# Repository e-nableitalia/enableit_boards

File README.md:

# enable-it
e-Nable Italia Bionic Platform

This project aims to create a general purpose hardware platform that can be used to develop bionic/electronics controlled devices

## Boards
### Controllers - controller boards with a general purpose CPU, exposing a standard bus interface (see B2BCB specifications)
* ESP32 Wroom board Rev. B - ESP32 S3 based 

### Debug - debug, testing boards
* Debug Board Rev. A, mating board useful for debug and testing purposes

## Project directory layout
- docs, contains general documents
- schematics,  contains schematics in PDF format
- build, contains CAM Output files for board production
- EAGLE, contains project EAGLE files

## Project updates
220913 - repo init, added project doc & rev. 0.9 of ESP32 controller board

220922 - added debug board, added Rev. B of control board

220927 - updated debug board to Rev. A (added bottom connectors to allow tests of stacked boards)

230305 - added EMG Module - Rev B, changed name to enable-it

## KNOWN ISSUES

- ESP32 Controller board flash programming problem, rework required to fix this issue 
- Power connectors are not correctly aligned in all the boards, rework required to fix this issue
- Wrong height of 40pin connectors (4mm instead of 3mm)
- EMG Module power issue: short circuitt between AVDD & AVSS (PS$32 AVSS connected to V+ instead of V-)

## LIMITATION OF LIABILITY.
UNDER NO CIRCUMSTANCES AND UNDER NO LEGAL THEORY, WHETHER TORT (INCLUDING NEGLIGENCE), CONTRACT, OR OTHERWISE, SHALL YOU, THE INITIAL DEVELOPER, ANY OTHER CONTRIBUTOR, OR ANY DISTRIBUTOR OF COVERED CODE, OR ANY SUPPLIER OF ANY OF SUCH PARTIES, BE LIABLE TO ANY PERSON FOR ANY INDIRECT, SPECIAL, INCIDENTAL, OR CONSEQUENTIAL DAMAGES OF ANY CHARACTER INCLUDING, WITHOUT LIMITATION, DAMAGES FOR LOSS OF GOODWILL, WORK STOPPAGE, COMPUTER FAILURE OR MALFUNCTION, OR ANY AND ALL OTHER COMMERCIAL DAMAGES OR LOSSES, EVEN IF SUCH PARTY SHALL HAVE BEEN INFORMED OF THE POSSIBILITY OF SUCH DAMAGES. THIS LIMITATION OF LIABILITY SHALL NOT APPLY TO LIABILITY FOR DEATH OR PERSONAL INJURY RESULTING FROM SUCH PARTY'S NEGLIGENCE TO THE EXTENT APPLICABLE LAW PROHIBITS SUCH LIMITATION. SOME JURISDICTIONS DO NOT ALLOW THE EXCLUSION OR LIMITATION OF INCIDENTAL OR CONSEQUENTIAL DAMAGES, SO THIS EXCLUSION AND LIMITATION MAY NOT APPLY TO YOU.

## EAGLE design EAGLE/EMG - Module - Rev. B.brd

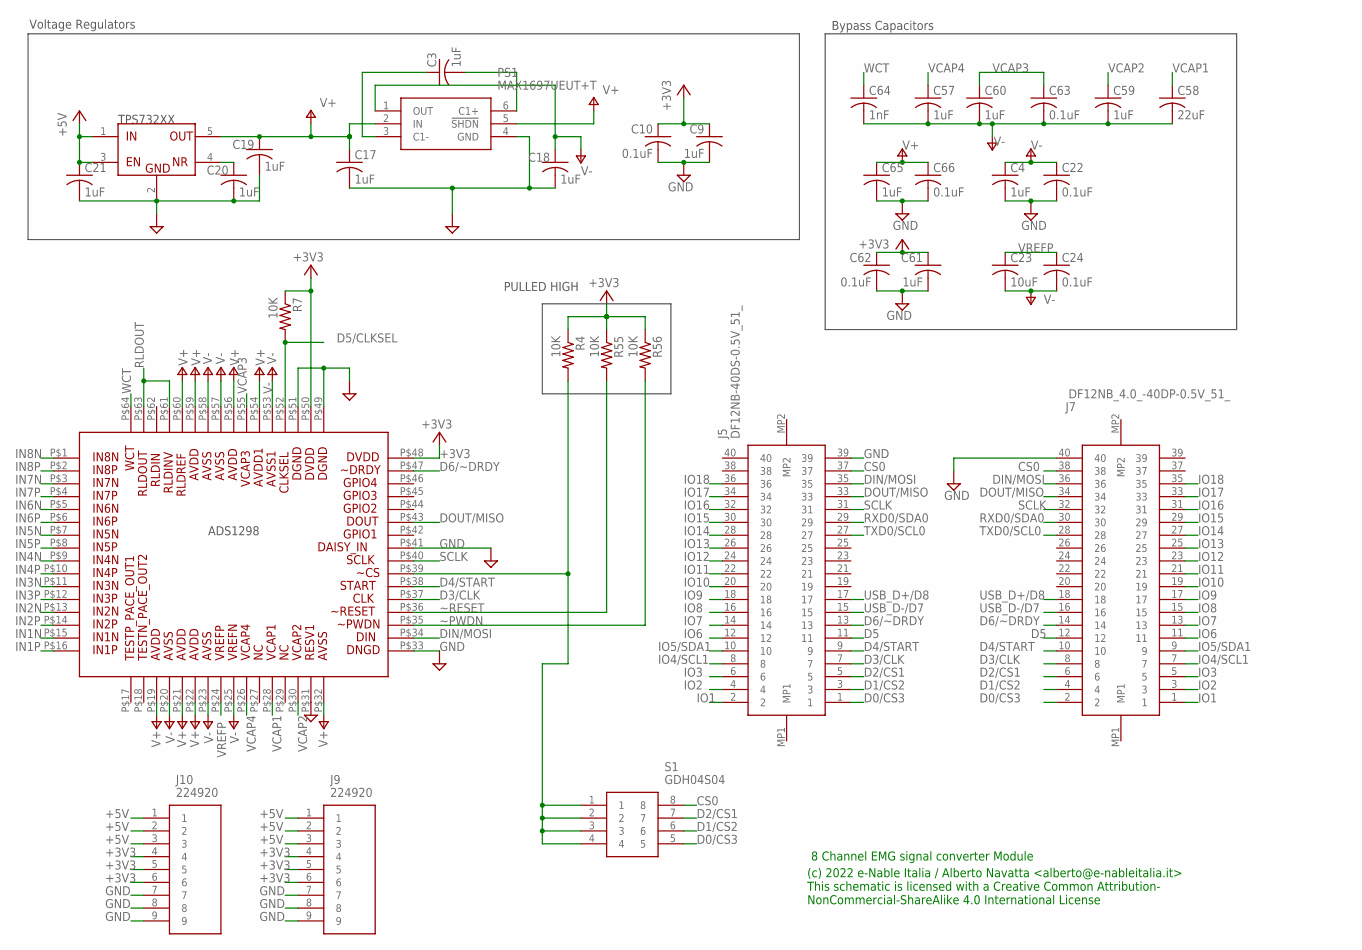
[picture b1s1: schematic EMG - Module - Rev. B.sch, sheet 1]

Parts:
C3, C4, C9, C17, C18, C19, C20, C21, C57, C59, C60, C61, C65: 1uF; C0402
C10, C22, C24, C62, C63, C66: 0.1uF; C0402
C23: 10uF; C0402
C58: 22uF; C0402
C64: 1nF; C0402
J5: DF12NB-40DS-0.5V_51_; DF12NB40DS05V51
J7: DF12NB_4.0_-40DP-0.5V_51_; DF12NB4040DP05V51
J9, J10: 224920
PS1: MAX1697UEUT+T; SOT95P280X145-6N
R4, R7, R55, R56: 10K; R0402
S1: GDH04S04; SOIC127P813X256-8N
U1: U1; TQFP-64
U21: TPS732XX; SOT23-5

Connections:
+3V3: C9.1, C10.1, C61.1, C62.1, J9.4, J9.5, J9.6, J10.4, J10.5, J10.6, R4.1, R7.1, R55.1, R56.1, U1.P$48, U1.P$50
+5V: C21.1, J9.1, J9.2, J9.3, J10.1, J10.2, J10.3, U21.1 (IN), U21.3 (EN)
CS0: J5.37, J7.38, S1.8
D0/CS3: J5.1, J7.2, S1.5
D1/CS2: J5.3, J7.4, S1.6
D2/CS1: J5.5, J7.6, S1.7
D3/CLK: J5.7, J7.8, U1.P$37
D4/START: J5.9, J7.10, U1.P$38
D5: J5.11, J7.12
D5/CLKSEL: R7.2, U1.P$52
D6/~DRDY: J5.13, J7.14, U1.P$47
DIN/MOSI: J5.35, J7.36, U1.P$34
DOUT/MISO: J5.33, J7.34, U1.P$43
GND: C4.2, C9.2, C10.2, C17.2, C18.2, C19.2, C20.2, C21.2, C22.2, C61.2, C62.2, C65.2, C66.2, J5.39, J7.40, J9.7, J9.8, J9.9, J10.7, J10.8, J10.9, PS1.4 (GND), U1.P$31, U1.P$33, U1.P$41, U1.P$49, U1.P$51, U21.2 (GND); also elsewhere on the board
IN1N: U1.P$15; also elsewhere on the board
IN1P: U1.P$16; also elsewhere on the board
IN2N: U1.P$13; also elsewhere on the board
IN2P: U1.P$14; also elsewhere on the board
IN3N: U1.P$11; also elsewhere on the board
IN3P: U1.P$12; also elsewhere on the board
IN4N: U1.P$9; also elsewhere on the board
IN4P: U1.P$10; also elsewhere on the board
IN5N: U1.P$7; also elsewhere on the board
IN5P: U1.P$8; also elsewhere on the board
IN6N: U1.P$5; also elsewhere on the board
IN6P: U1.P$6; also elsewhere on the board
IN7N: U1.P$3; also elsewhere on the board
IN7P: U1.P$4; also elsewhere on the board
IN8N: U1.P$1; also elsewhere on the board
IN8P: U1.P$2; also elsewhere on the board
IO1: J5.2, J7.1
IO2: J5.4, J7.3
IO3: J5.6, J7.5
IO4/SCL1: J5.8, J7.7
IO5/SDA1: J5.10, J7.9
IO6: J5.12, J7.11
IO7: J5.14, J7.13
IO8: J5.16, J7.15
IO9: J5.18, J7.17
IO10: J5.20, J7.19
IO11: J5.22, J7.21
IO12: J5.24, J7.23
IO13: J5.26, J7.25
IO14: J5.28, J7.27
IO15: J5.30, J7.29
IO16: J5.32, J7.31
IO17: J5.34, J7.33
IO18: J5.36, J7.35
unnamed: C3.1, PS1.3 (C1-)
unnamed: C3.2, PS1.6 (C1+)
unnamed: C20.1, U21.4 (NR)
RLDOUT: U1.P$61, U1.P$63; also elsewhere on the board
RXD0/SDA0: J5.29, J7.30
SCLK: J5.31, J7.32, U1.P$40
TXD0/SCL0: J5.27, J7.28
USB_D+/D8: J5.17, J7.18
USB_D-/D7: J5.15, J7.16
V+: C17.1, C19.1, C65.1, C66.1, PS1.2 (IN), PS1.5 (!SHDN), U1.P$19, U1.P$21, U1.P$22, U1.P$32, U1.P$54, U1.P$56, U1.P$59, U1.P$60, U21.5 (OUT)
V-: C4.1, C18.1, C22.1, C23.2, C24.2, C57.2, C58.2, C59.2, C60.2, C63.2, C64.2, PS1.1 (OUT), U1.P$20, U1.P$23, U1.P$25, U1.P$53, U1.P$57, U1.P$58
VCAP1: C58.1, U1.P$28
VCAP2: C59.1, U1.P$30
VCAP3: C60.1, C63.1, U1.P$55
VCAP4: C57.1, U1.P$26
VREFP: C23.1, C24.1, U1.P$24
WCT: C64.1, U1.P$64
~CS: R4.2, S1.1, S1.2, S1.3, S1.4, U1.P$39
~PWDN: R56.2, U1.P$35
~RESET: R55.2, U1.P$36

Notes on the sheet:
PULLED HIGH
Voltage Regulators
Bypass Capacitors
(c) 2022 e-Nable Italia / Alberto Navatta <alberto@e-nableitalia.it> This schematic is licensed with a Creative Common Attribution- NonCommercial-ShareAlike 4.0 International License
8 Channel EMG signal converter Module

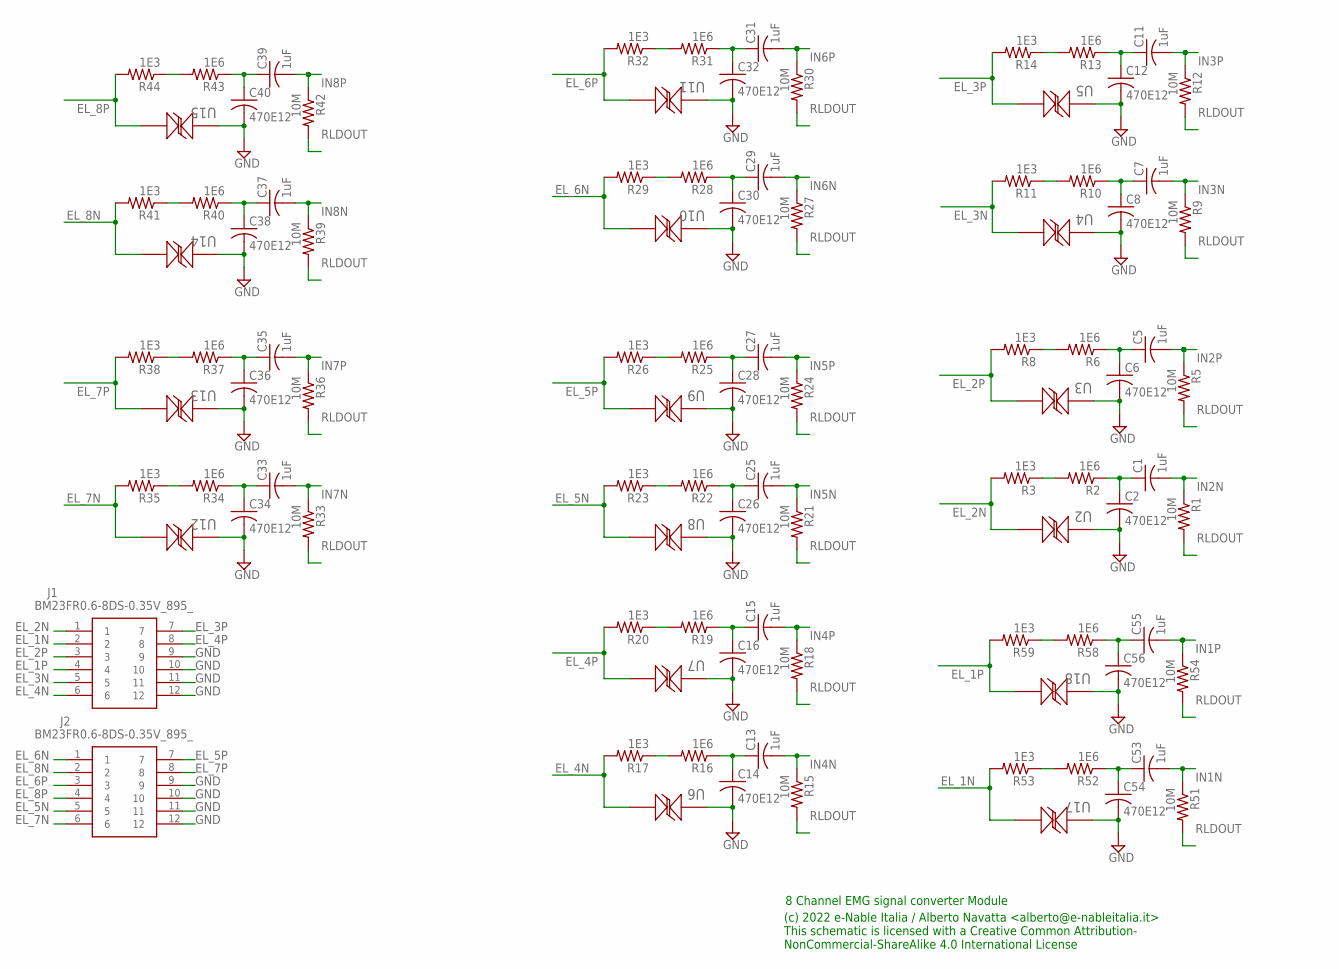
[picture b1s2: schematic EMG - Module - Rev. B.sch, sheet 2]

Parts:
C1, C5, C7, C11, C13, C15, C25, C27, C29, C31, C33, C35, C37, C39, C53, C55: 1uF; C0402
C2, C6, C8, C12, C14, C16, C26, C28, C30, C32, C34, C36, C38, C40, C54, C56: 470E12; C0402
J1, J2: BM23FR0.6-8DS-0.35V_895_; BM23FR068DS035V895
R1, R5, R9, R12, R15, R18, R21, R24, R27, R30, R33, R36, R39, R42, R51, R54: 10M; R0402
R2, R6, R10, R13, R16, R19, R22, R25, R28, R31, R34, R37, R40, R43, R52, R58: 1E6; R0402
R3, R8, R11, R14, R17, R20, R23, R26, R29, R32, R35, R38, R41, R44, R53, R59: 1E3; R0402
U2: U2; DPY0002A
U3: U3; DPY0002A
U4: U4; DPY0002A
U5: U5; DPY0002A
U6: U6; DPY0002A
U7: U7; DPY0002A
U8: U8; DPY0002A
U9: U9; DPY0002A
U10: U10; DPY0002A
U11, U18: U18; DPY0002A
U12: U12; DPY0002A
U13: U13; DPY0002A
U14: U14; DPY0002A
U15: U15; DPY0002A
U17: U17; DPY0002A

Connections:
EL_1N: J1.2, R53.2, U17.2
EL_1P: J1.4, R59.2, U18.2
EL_2N: J1.1, R3.2, U2.2
EL_2P: J1.3, R8.2, U3.2
EL_3N: J1.5, R11.2, U4.2
EL_3P: J1.7, R14.2, U5.2
EL_4N: J1.6, R17.2, U6.2
EL_4P: J1.8, R20.2, U7.2
EL_5N: J2.5, R23.2, U8.2
EL_5P: J2.7, R26.2, U9.2
EL_6N: J2.1, R29.2, U10.2
EL_6P: J2.3, R32.2, U11.2
EL_7N: J2.6, R35.2, U12.2
EL_7P: J2.8, R38.2, U13.2
EL_8N: J2.2, R41.2, U14.2
EL_8P: J2.4, R44.2, U15.2
GND: C2.2, C6.2, C8.2, C12.2, C14.2, C16.2, C26.2, C28.2, C30.2, C32.2, C34.2, C36.2, C38.2, C40.2, C54.2, C56.2, J1.9, J1.10, J1.11, J1.12, J2.9, J2.10, J2.11, J2.12, U2.1, U3.1, U4.1, U5.1, U6.1, U7.1, U8.1, U9.1, U10.1, U11.1, U12.1, U13.1, U14.1, U15.1, U17.1, U18.1; also elsewhere on the board
IN1N: C53.2, R51.1; also elsewhere on the board
IN1P: C55.2, R54.1; also elsewhere on the board
IN2N: C1.2, R1.1; also elsewhere on the board
IN2P: C5.2, R5.1; also elsewhere on the board
IN3N: C7.2, R9.1; also elsewhere on the board
IN3P: C11.2, R12.1; also elsewhere on the board
IN4N: C13.2, R15.1; also elsewhere on the board
IN4P: C15.2, R18.1; also elsewhere on the board
IN5N: C25.2, R21.1; also elsewhere on the board
IN5P: C27.2, R24.1; also elsewhere on the board
IN6N: C29.2, R27.1; also elsewhere on the board
IN6P: C31.2, R30.1; also elsewhere on the board
IN7N: C33.2, R33.1; also elsewhere on the board
IN7P: C35.2, R36.1; also elsewhere on the board
IN8N: C37.2, R39.1; also elsewhere on the board
IN8P: C39.2, R42.1; also elsewhere on the board
unnamed: C1.1, C2.1, R2.1
unnamed: R2.2, R3.1
unnamed: C5.1, C6.1, R6.1
unnamed: R6.2, R8.1
unnamed: C7.1, C8.1, R10.1
unnamed: R10.2, R11.1
unnamed: C11.1, C12.1, R13.1
unnamed: R13.2, R14.1
unnamed: C13.1, C14.1, R16.1
unnamed: R16.2, R17.1
unnamed: C15.1, C16.1, R19.1
unnamed: R19.2, R20.1
unnamed: C25.1, C26.1, R22.1
unnamed: R22.2, R23.1
unnamed: C27.1, C28.1, R25.1
unnamed: R25.2, R26.1
unnamed: C29.1, C30.1, R28.1
unnamed: R28.2, R29.1
unnamed: C31.1, C32.1, R31.1
unnamed: R31.2, R32.1
unnamed: C33.1, C34.1, R34.1
unnamed: R34.2, R35.1
unnamed: C35.1, C36.1, R37.1
unnamed: R37.2, R38.1
unnamed: C37.1, C38.1, R40.1
unnamed: R40.2, R41.1
unnamed: C39.1, C40.1, R43.1
unnamed: R43.2, R44.1
unnamed: C53.1, C54.1, R52.1
unnamed: R52.2, R53.1
unnamed: C55.1, C56.1, R58.1
unnamed: R58.2, R59.1
RLDOUT: R1.2, R5.2, R9.2, R12.2, R15.2, R18.2, R21.2, R24.2, R27.2, R30.2, R33.2, R36.2, R39.2, R42.2, R51.2, R54.2; also elsewhere on the board

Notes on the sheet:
(c) 2022 e-Nable Italia / Alberto Navatta <alberto@e-nableitalia.it> This schematic is licensed with a Creative Common Attribution- NonCommercial-ShareAlike 4.0 International License
8 Channel EMG signal converter Module

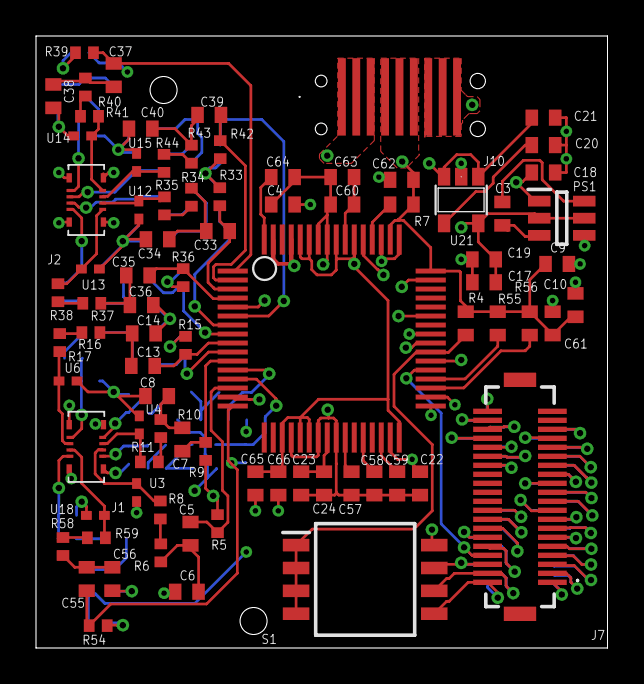
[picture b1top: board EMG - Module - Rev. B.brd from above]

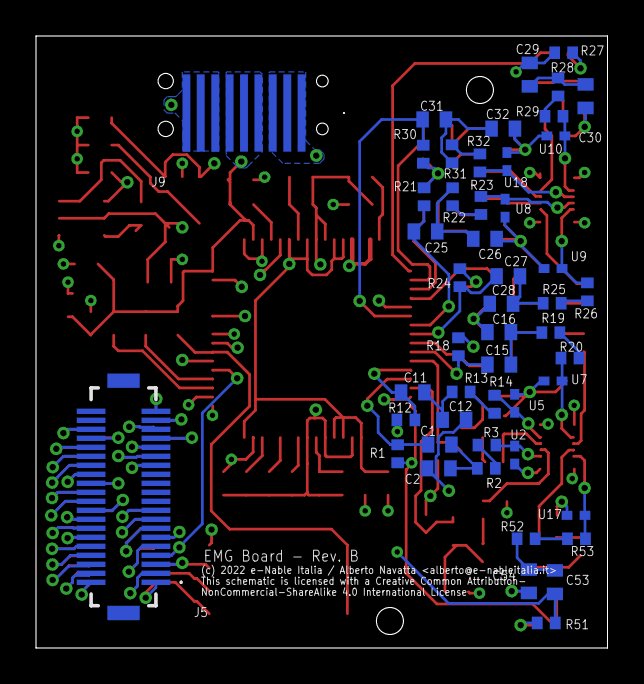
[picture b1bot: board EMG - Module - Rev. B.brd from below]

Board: 4 copper layers, 31.8 x 34.0 mm, 132 parts (50 on the bottom side), 116 nets.

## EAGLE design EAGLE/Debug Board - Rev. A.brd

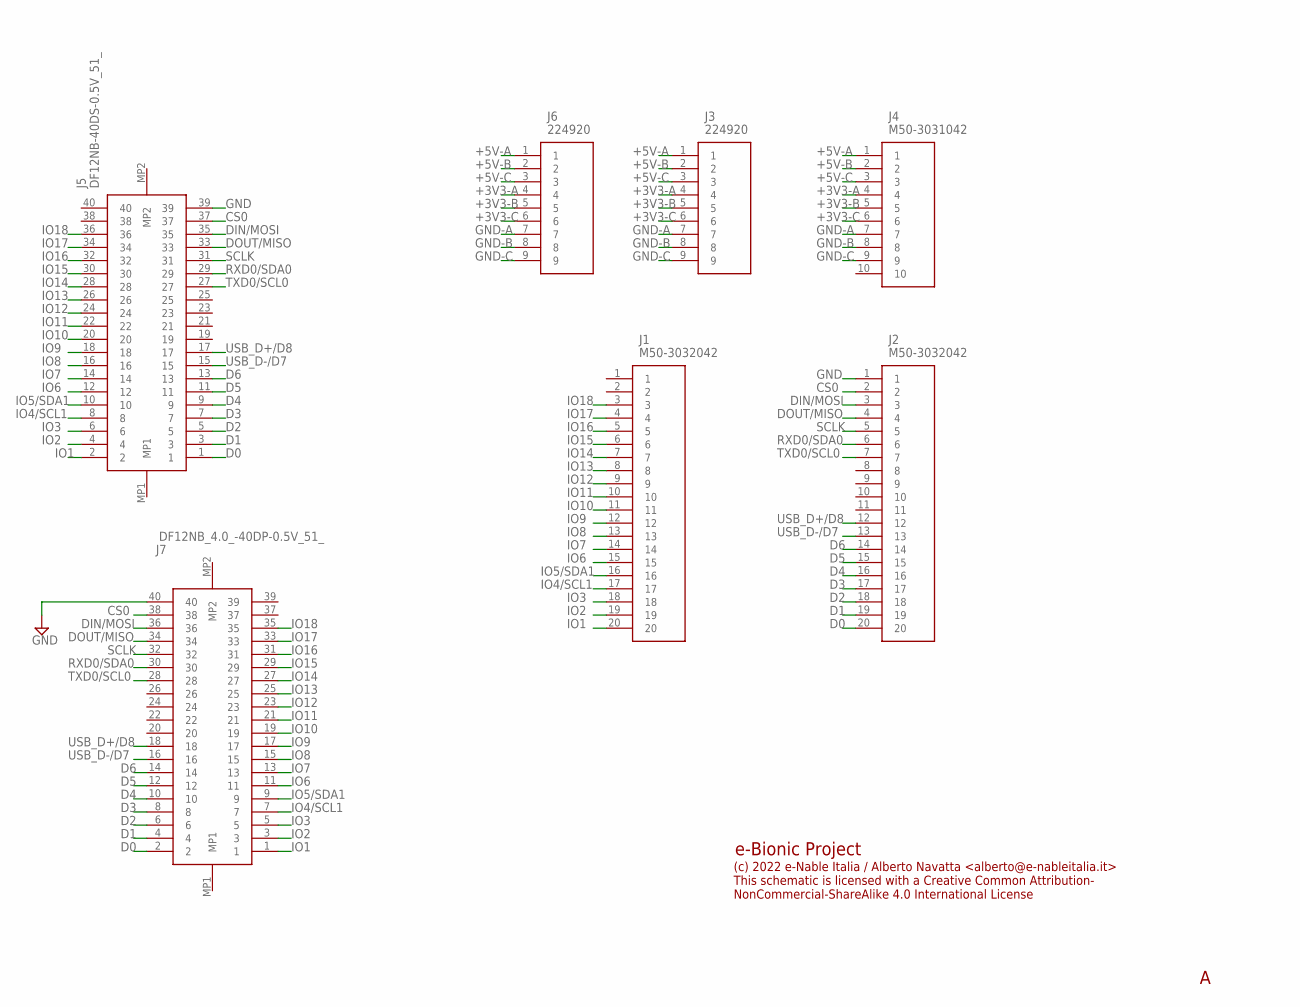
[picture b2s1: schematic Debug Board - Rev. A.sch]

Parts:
J1, J2: M50-3032042; M503032042
J3, J6: 224920
J4: M50-3031042; M503031042
J5: DF12NB-40DS-0.5V_51_; DF12NB40DS05V51
J7: DF12NB_4.0_-40DP-0.5V_51_; DF12NB4040DP05V51

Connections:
+3V3-A: J3.4, J4.4, J6.4
+3V3-B: J3.5, J4.5, J6.5
+3V3-C: J3.6, J4.6, J6.6
+5V-A: J3.1, J4.1, J6.1
+5V-B: J3.2, J4.2, J6.2
+5V-C: J3.3, J4.3, J6.3
CS0: J2.2, J5.37, J7.38
D0: J2.20, J5.1, J7.2
D1: J2.19, J5.3, J7.4
D2: J2.18, J5.5, J7.6
D3: J2.17, J5.7, J7.8
D4: J2.16, J5.9, J7.10
D5: J2.15, J5.11, J7.12
D6: J2.14, J5.13, J7.14
DIN/MOSI: J2.3, J5.35, J7.36
DOUT/MISO: J2.4, J5.33, J7.34
GND: J2.1, J5.39, J7.40
GND-A: J3.7, J4.7, J6.7
GND-B: J3.8, J4.8, J6.8
GND-C: J3.9, J4.9, J6.9
IO1: J1.20, J5.2, J7.1
IO2: J1.19, J5.4, J7.3
IO3: J1.18, J5.6, J7.5
IO4/SCL1: J1.17, J5.8, J7.7
IO5/SDA1: J1.16, J5.10, J7.9
IO6: J1.15, J5.12, J7.11
IO7: J1.14, J5.14, J7.13
IO8: J1.13, J5.16, J7.15
IO9: J1.12, J5.18, J7.17
IO10: J1.11, J5.20, J7.19
IO11: J1.10, J5.22, J7.21
IO12: J1.9, J5.24, J7.23
IO13: J1.8, J5.26, J7.25
IO14: J1.7, J5.28, J7.27
IO15: J1.6, J5.30, J7.29
IO16: J1.5, J5.32, J7.31
IO17: J1.4, J5.34, J7.33
IO18: J1.3, J5.36, J7.35
RXD0/SDA0: J2.6, J5.29, J7.30
SCLK: J2.5, J5.31, J7.32
TXD0/SCL0: J2.7, J5.27, J7.28
USB_D+/D8: J2.12, J5.17, J7.18
USB_D-/D7: J2.13, J5.15, J7.16

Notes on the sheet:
e-Bionic Project
(c) 2022 e-Nable Italia / Alberto Navatta <alberto@e-nableitalia.it> This schematic is licensed with a Creative Common Attribution- NonCommercial-ShareAlike 4.0 International License

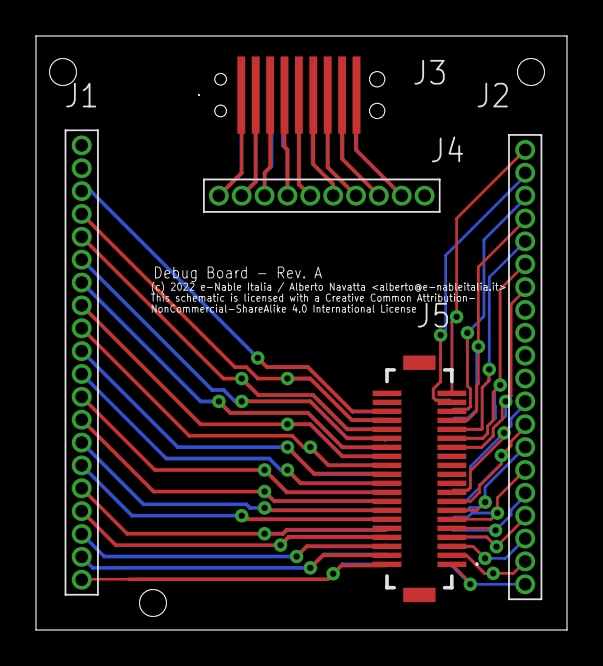
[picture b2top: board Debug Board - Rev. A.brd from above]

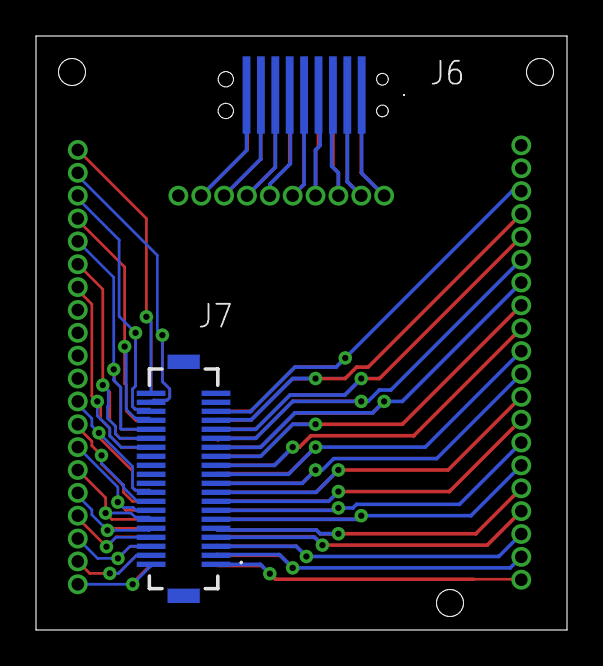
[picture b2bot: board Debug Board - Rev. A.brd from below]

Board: 2 copper layers, 29.5 x 33.0 mm, 7 parts (2 on the bottom side), 43 nets.

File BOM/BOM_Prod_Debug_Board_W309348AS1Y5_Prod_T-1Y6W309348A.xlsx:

|  |  | W309348AS1Y7 T-1Y8W309348A 05PCS BOM (Bill of Materials)
Item # | *Designator | *Qty | Manufacturer | *Mfg Part # | Description / Value | *Package/Footprint | Type | Your Instructions / Notes
1 | J3, J6 | 2 | ERNI | 224920 | Board to Board & Mezzanine Connectors 9P 0.8MM VERT FML CLASS 4 3MM SMT | 224920 | SMD
2 | J5 | 1 | Hirose | DF12NB-40DS-0.5V(51) | Board to Board & Mezzanine Connectors CONN RCPT 40POS SMD | DF12NB40DS05V51 | SMD
3 | J7 | 1 | Hirose | DF12NB(4.0)-40DP-0.5V(51) | Board to Board & Mezzanine Connectors CONN HDR 40POS SMD G | DF12NB4040DP05V51 | SMD
4 | J4 | 1 | Harwin | M50-3031042 | Headers & Wire Housings 10 WAY SIL VERT PC TAIL SKT | M503031042 | DNS | Do not populate
5 | J1, J2 | 2 | Harwin | M50-3032042 | Headers & Wire Housings 20 WAY SIL VERT PC TAIL SKT | M503032042 | DNS | Do not populate
6
7
8
9
10
11
12
13
14
15
16
17
18
19
20
21
22
23
24
25
26
27
Need a quick and accurante quote? Need an efficient production? Please read SMT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
Click for Instructions on How to Create a BOM

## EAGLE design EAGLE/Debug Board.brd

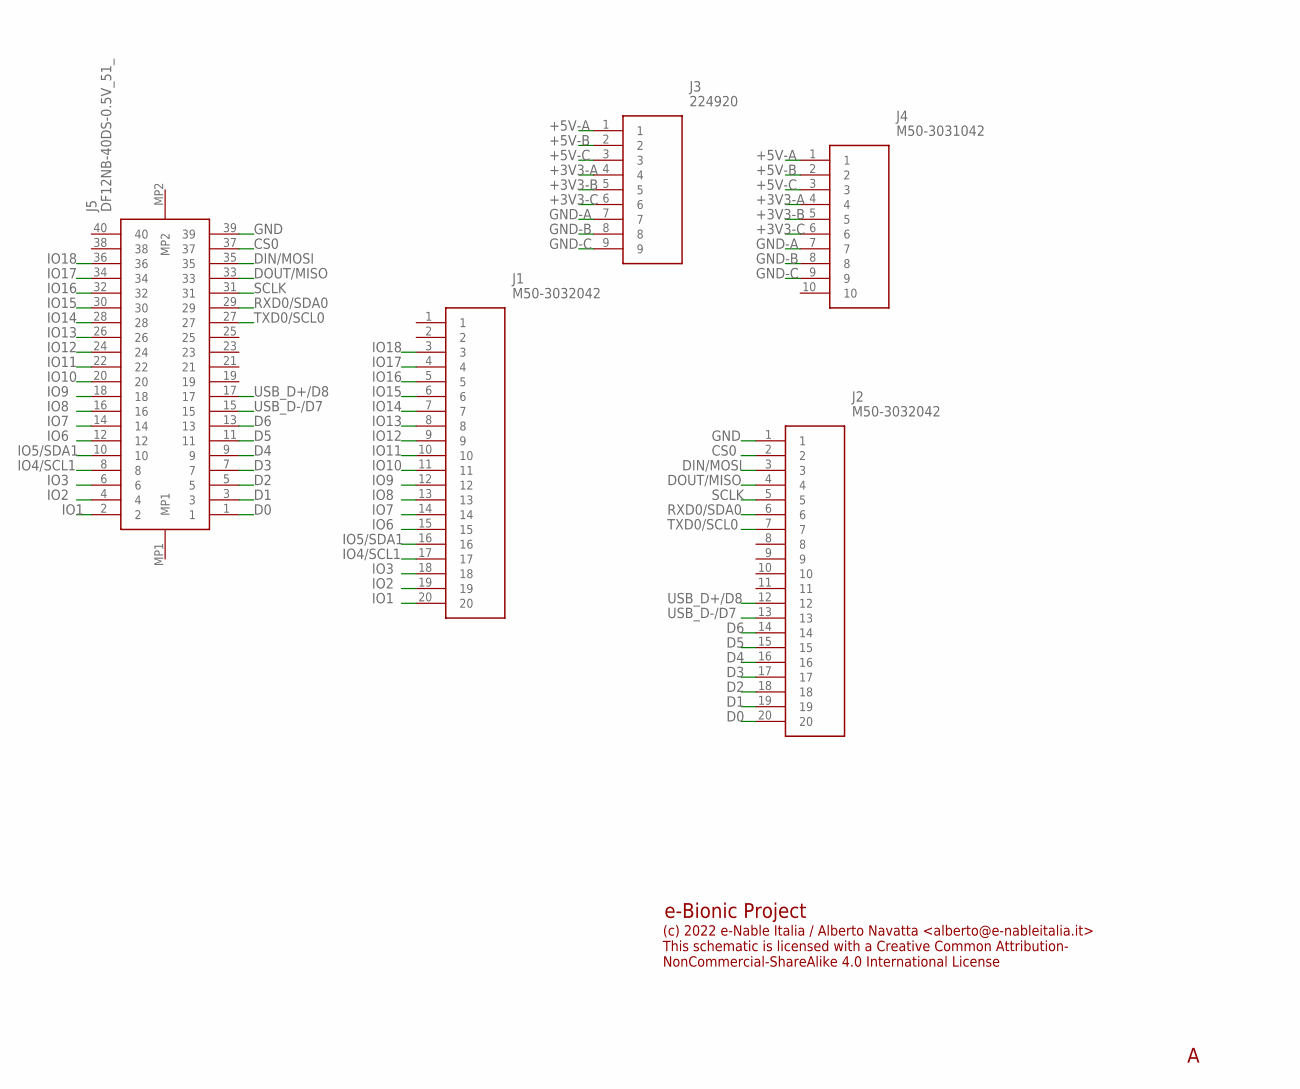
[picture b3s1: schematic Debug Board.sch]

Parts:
J1, J2: M50-3032042; M503032042
J3: 224920
J4: M50-3031042; M503031042
J5: DF12NB-40DS-0.5V_51_; DF12NB40DS05V51

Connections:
+3V3-A: J3.4, J4.4
+3V3-B: J3.5, J4.5
+3V3-C: J3.6, J4.6
+5V-A: J3.1, J4.1
+5V-B: J3.2, J4.2
+5V-C: J3.3, J4.3
CS0: J2.2, J5.37
D0: J2.20, J5.1
D1: J2.19, J5.3
D2: J2.18, J5.5
D3: J2.17, J5.7
D4: J2.16, J5.9
D5: J2.15, J5.11
D6: J2.14, J5.13
DIN/MOSI: J2.3, J5.35
DOUT/MISO: J2.4, J5.33
GND: J2.1, J5.39
GND-A: J3.7, J4.7
GND-B: J3.8, J4.8
GND-C: J3.9, J4.9
IO1: J1.20, J5.2
IO2: J1.19, J5.4
IO3: J1.18, J5.6
IO4/SCL1: J1.17, J5.8
IO5/SDA1: J1.16, J5.10
IO6: J1.15, J5.12
IO7: J1.14, J5.14
IO8: J1.13, J5.16
IO9: J1.12, J5.18
IO10: J1.11, J5.20
IO11: J1.10, J5.22
IO12: J1.9, J5.24
IO13: J1.8, J5.26
IO14: J1.7, J5.28
IO15: J1.6, J5.30
IO16: J1.5, J5.32
IO17: J1.4, J5.34
IO18: J1.3, J5.36
RXD0/SDA0: J2.6, J5.29
SCLK: J2.5, J5.31
TXD0/SCL0: J2.7, J5.27
USB_D+/D8: J2.12, J5.17
USB_D-/D7: J2.13, J5.15

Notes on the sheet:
e-Bionic Project
(c) 2022 e-Nable Italia / Alberto Navatta <alberto@e-nableitalia.it> This schematic is licensed with a Creative Common Attribution- NonCommercial-ShareAlike 4.0 International License

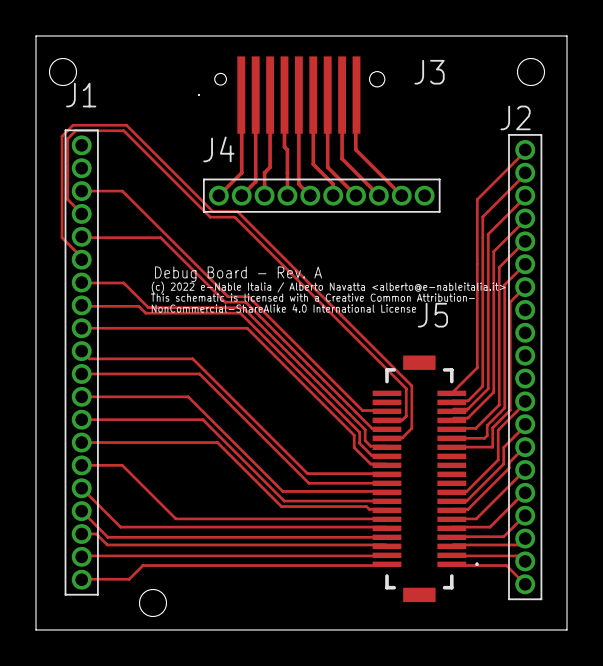
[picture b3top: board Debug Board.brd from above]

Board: 2 copper layers, 29.5 x 33.0 mm, 5 parts (0 on the bottom side), 43 nets.

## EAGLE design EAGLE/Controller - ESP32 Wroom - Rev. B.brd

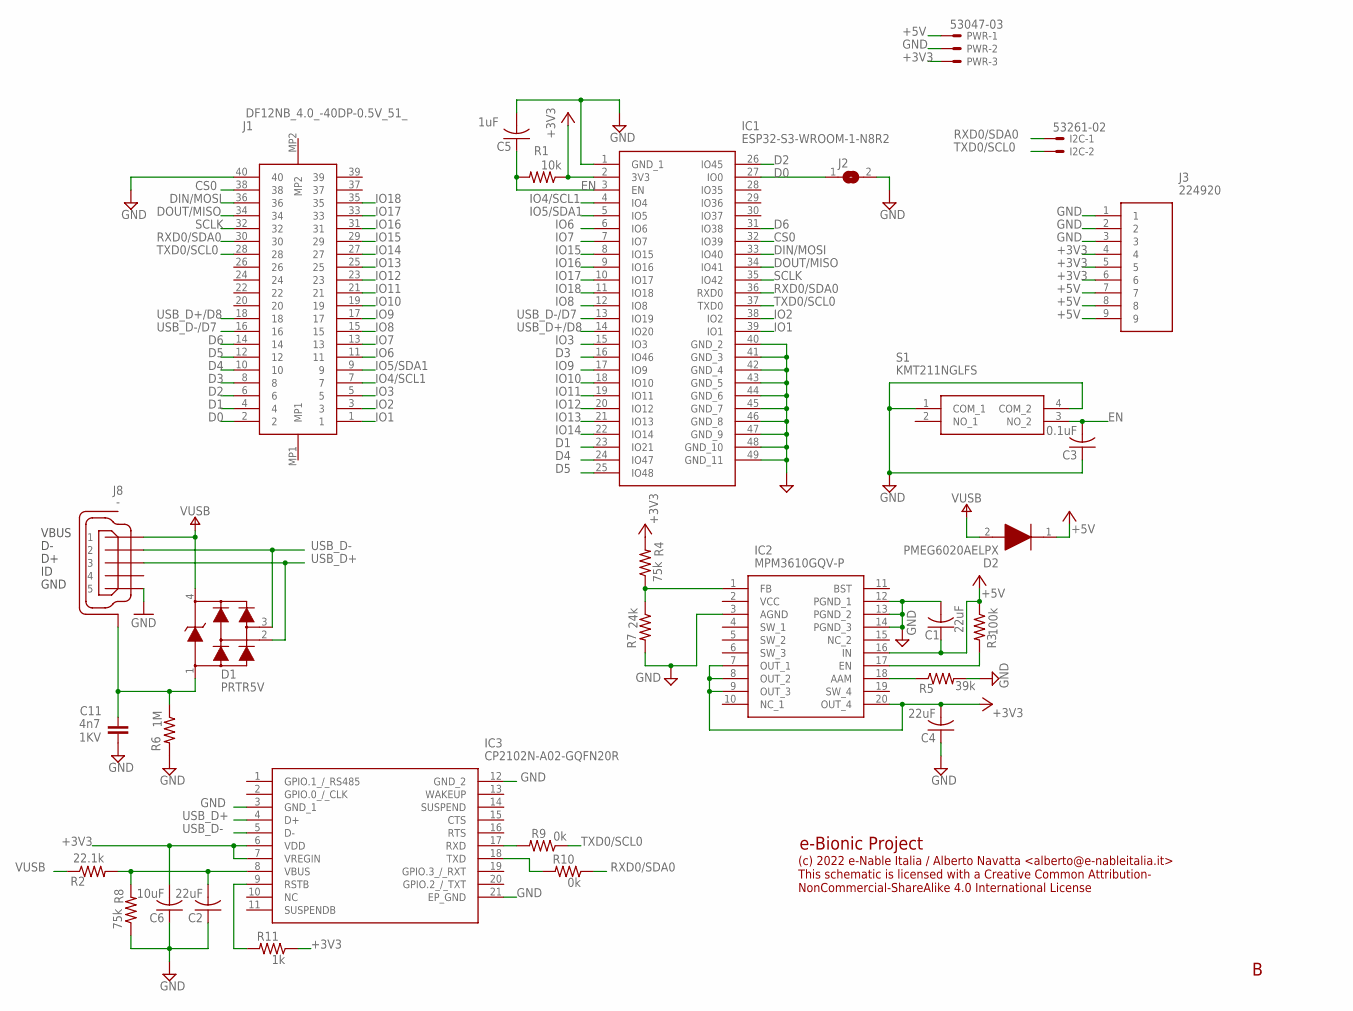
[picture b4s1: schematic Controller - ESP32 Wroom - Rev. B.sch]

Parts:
C1, C4: 22uF; C0603
C2: 22uF; C0402
C3: 0.1uF; C0402
C5: 1uF; C0402
C6: 10uF; C0402
C11: 4n7; 0805-R2013X50N; VOLTAGE 1KV
D1: PRTR5V; SOT190P230X110-4N
D2: PMEG6020AELPX; SODFL4725X110N
I2C: 53261-02
IC1: ESP32-S3-WROOM-1-N8R2; ESP32S3WROOM1N8R2
IC2: MPM3610GQV-P; MPM3610GQVP
IC3: CP2102N-A02-GQFN20R; CP2102NA02GQFN20
J1: DF12NB_4.0_-40DP-0.5V_51_; DF12NB4040DP05V51
J2: SJ
J3: 224920
J8: -; ZX62-AB-5PA
PWR: 53047-03
R1: 10k; R0402
R2: 22.1k; R0402
R3: 100k; R0402
R4, R8: 75k; R0402
R5: 39k; R0402
R6: 1M; R0402
R7: 24k; R0402
R9, R10: 0k; R0402
R11: 1k; R0402
S1: KMT211NGLFS

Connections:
+3V3: C4.2, C6.2, IC1.2 (3V3), IC2.7 (OUT_1), IC2.8 (OUT_2), IC2.9 (OUT_3), IC2.20 (OUT_4), IC3.6 (VDD), IC3.7 (VREGIN), J3.4, J3.5, J3.6, PWR.3, R1.1, R4.2, R11.1
+5V: C1.1, D2.1 (K), IC2.16 (IN), J3.7, J3.8, J3.9, PWR.1, R3.1
CS0: IC1.32 (IO39), J1.38
D0: IC1.27 (IO0), J1.2, J2.1
D1: IC1.23 (IO21), J1.4
D2: IC1.26 (IO45), J1.6
D3: IC1.16 (IO46), J1.8
D4: IC1.24 (IO47), J1.10
D5: IC1.25 (IO48), J1.12
D6: IC1.31 (IO38), J1.14
DIN/MOSI: IC1.33 (IO40), J1.36
DOUT/MISO: IC1.34 (IO41), J1.34
EN: C3.2, C5.1, IC1.3 (EN), R1.2, S1.3 (NO_2)
GND: C1.2, C2.1, C3.1, C4.1, C5.2, C6.1, C11.2, IC1.1 (GND_1), IC1.40 (GND_2), IC1.41 (GND_3), IC1.42 (GND_4), IC1.43 (GND_5), IC1.44 (GND_6), IC1.45 (GND_7), IC1.46 (GND_8), IC1.47 (GND_9), IC1.48 (GND_10), IC1.49 (GND_11), IC2.3 (AGND), IC2.12 (PGND_1), IC2.13 (PGND_2), IC2.14 (PGND_3), IC3.3 (GND_1), IC3.12 (GND_2), IC3.21 (EP_GND), J1.40, J2.2, J3.1, J3.2, J3.3, J8.5, PWR.2, R5.2, R6.2, R7.2, R8.1, S1.1 (COM_1), S1.4 (COM_2)
IO1: IC1.39 (IO1), J1.1
IO2: IC1.38 (IO2), J1.3
IO3: IC1.15 (IO3), J1.5
IO4/SCL1: IC1.4 (IO4), J1.7
IO5/SDA1: IC1.5 (IO5), J1.9
IO6: IC1.6 (IO6), J1.11
IO7: IC1.7 (IO7), J1.13
IO8: IC1.12 (IO8), J1.15
IO9: IC1.17 (IO9), J1.17
IO10: IC1.18 (IO10), J1.19
IO11: IC1.19 (IO11), J1.21
IO12: IC1.20 (IO12), J1.23
IO13: IC1.21 (IO13), J1.25
IO14: IC1.22 (IO14), J1.27
IO15: IC1.8 (IO15), J1.29
IO16: IC1.9 (IO16), J1.31
IO17: IC1.10 (IO17), J1.33
IO18: IC1.11 (IO18), J1.35
unnamed: IC2.18 (AAM), R5.1
unnamed: C2.2, IC3.8 (VBUS), R2.2, R8.2
unnamed: IC2.1 (FB), R4.1, R7.1
unnamed: IC2.17 (EN), R3.2
unnamed: IC3.17 (RXD), R9.2
unnamed: IC3.18 (TXD), R10.2
unnamed: C11.1, D1.1, J8.6 (SH), J8.7 (SH), J8.8 (SH), J8.9 (SH), J8.10 (SH), J8.11 (SH), R6.1
unnamed: IC3.9 (RSTB), R11.2
RXD0/SDA0: I2C.1, IC1.36 (RXD0), J1.30, R10.1
SCLK: IC1.35 (IO42), J1.32
TXD0/SCL0: I2C.2, IC1.37 (TXD0), J1.28, R9.1
USB_D+: D1.2, IC3.4 (D+), J8.3
USB_D+/D8: IC1.14 (IO20), J1.18
USB_D-: D1.3, IC3.5 (D-), J8.2
USB_D-/D7: IC1.13 (IO19), J1.16
VUSB: D1.4, D2.2 (A), J8.1, R2.1

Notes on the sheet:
e-Bionic Project
(c) 2022 e-Nable Italia / Alberto Navatta <alberto@e-nableitalia.it> This schematic is licensed with a Creative Common Attribution- NonCommercial-ShareAlike 4.0 International License

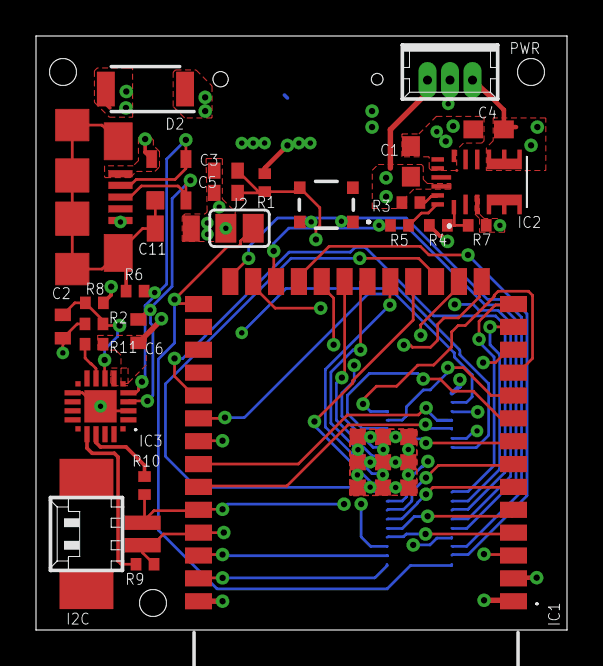
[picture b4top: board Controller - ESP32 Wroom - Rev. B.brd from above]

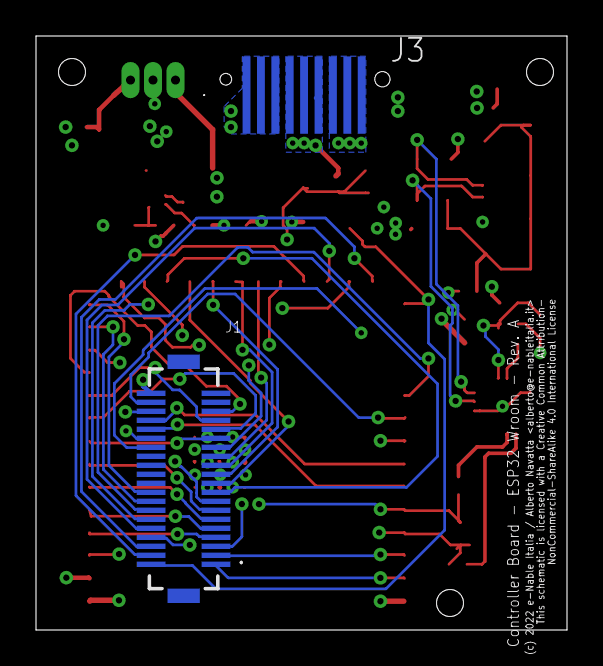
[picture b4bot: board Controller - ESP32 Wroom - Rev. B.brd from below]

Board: 4 copper layers, 29.5 x 33.0 mm, 30 parts (2 on the bottom side), 48 nets.

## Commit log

2022-09-13 Added project presentation
2022-09-13 Added latest release of ESP32 Controller board
2022-09-13 Update README.md
    updated readme
2022-09-13 Create License
2022-09-13 directory layout review
2022-09-13 Update README.md
    dir layout review
2022-09-18 [BION-1] completed review of controller board, changes
    1) Wrong side for power connector
    2) Removed signals from ground plane
    3) JTAG connector is optional, changed with a smal one to reduce footprint
2022-09-18 [BION-1] Added board and schematics PDF
2022-09-19 [BION-1] Removed old version files
    * removed Rev. 0.9 files
    * removed jtag connector, JTAG PINs can be extracted from J1 connector
2022-09-19 Added board revision & copyrights on PCB
2022-09-19 Fixed some clearance error
2022-09-19 Changed some via to be passthrought
    Added schematic and new board layout prints
2022-09-22 Added: * Rev. B Controller Board * Debug Board
2022-09-22 Added Rev. B Controller Board & Rev. A Debug Board
2022-09-27 Updated Debug Board to Rev. A:
    Added power and data bus connector on the bottom side of the board
2022-10-16 Added BOMs, fixed some typo in presentation
2023-03-05 Added EMG EMG - Module - Rev. B board, updated BOMs and build directory
2023-03-06 Updated readme and issue descriptions

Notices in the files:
parts and their libraries:
Arduino-connectors: Copyright (c) 2016-2017 Arduino LLC.  All right reserved.
COPYRIGHT: Copyright (C) 2022 Ultra Librarian. All rights reserved.
